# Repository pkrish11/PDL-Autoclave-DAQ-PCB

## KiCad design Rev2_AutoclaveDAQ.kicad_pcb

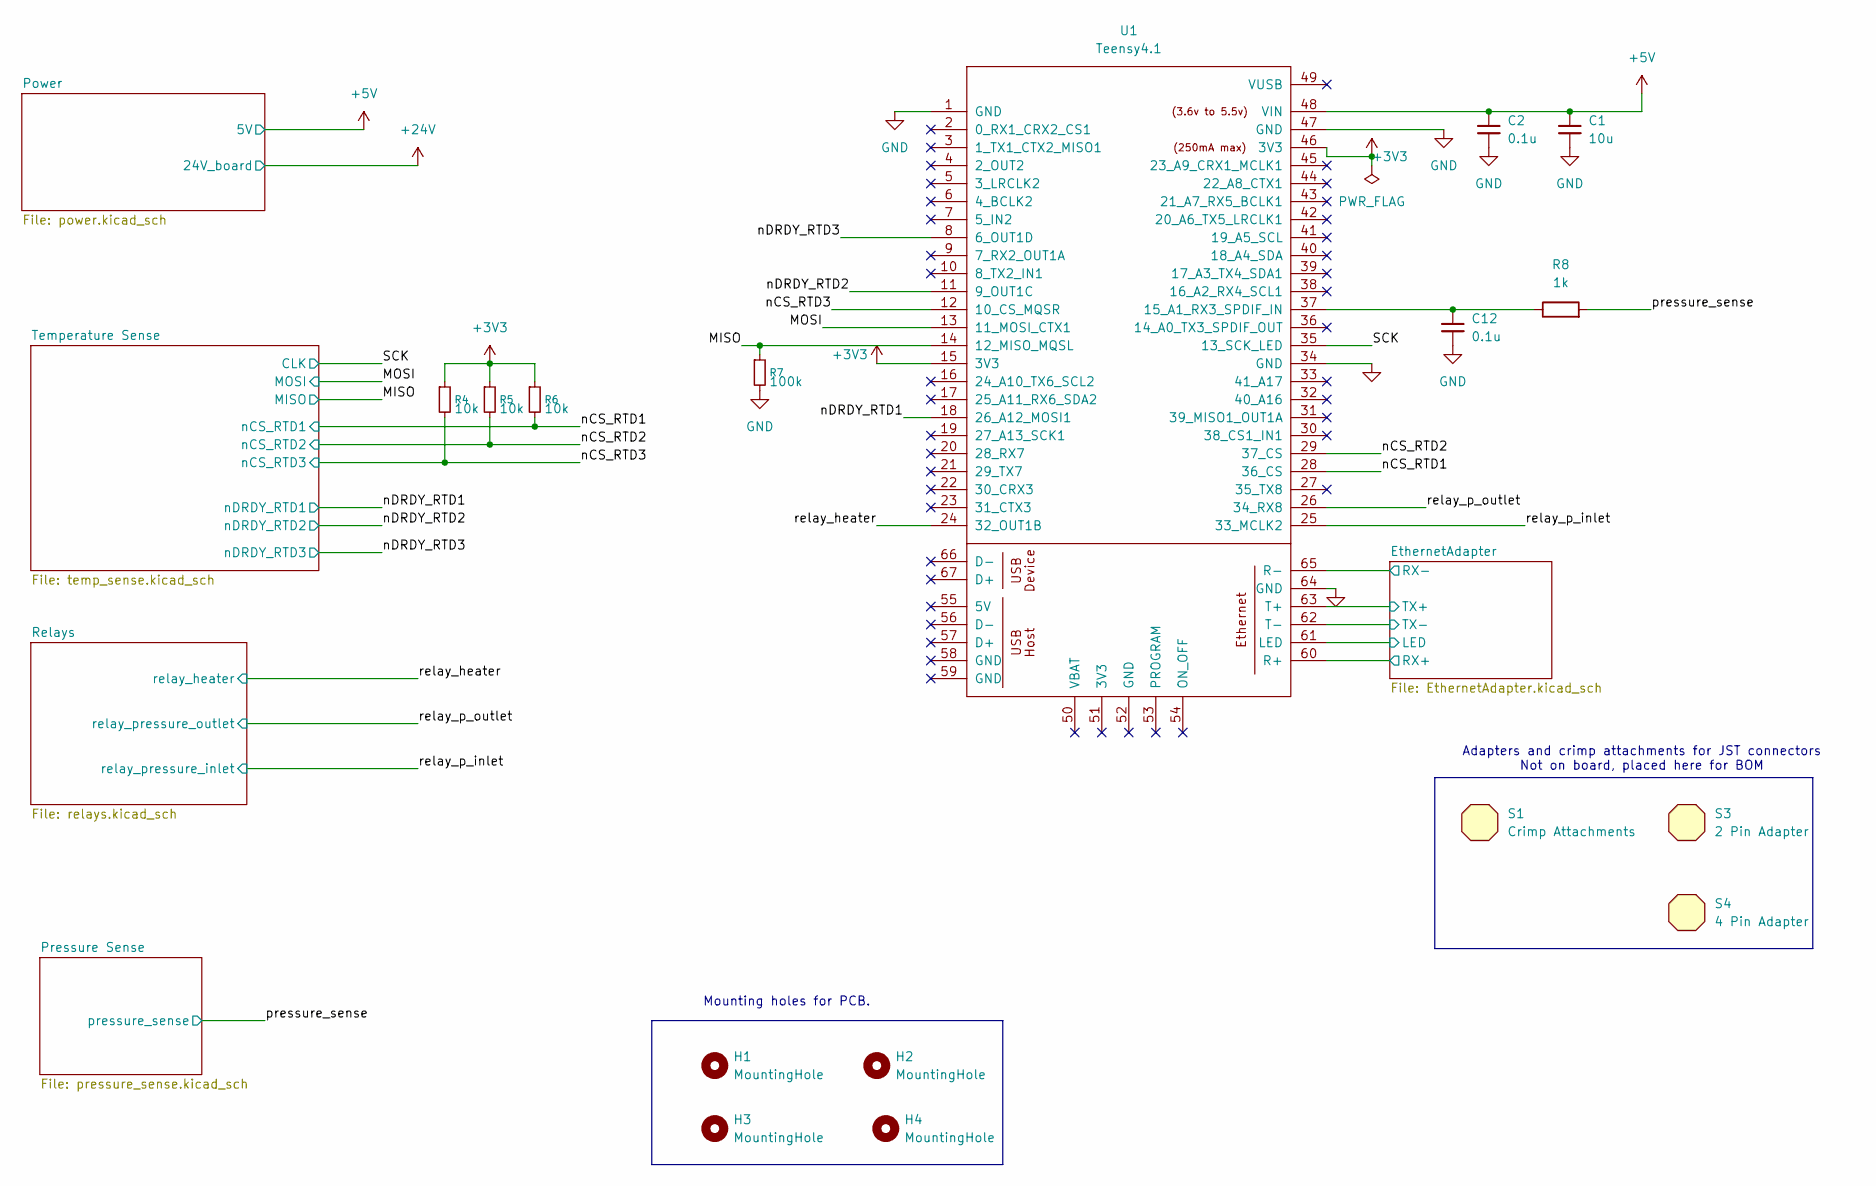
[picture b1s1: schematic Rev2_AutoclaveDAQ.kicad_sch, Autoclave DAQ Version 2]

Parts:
C1: 10u; C_0805_2012Metric; DigiKey_Part_Number 1276-2872-1-ND
C2, C12: 0.1u; C_0805_2012Metric; DigiKey_Part_Number 399-C0805C104K5RACTUCT-ND
H1, H2, H3, H4: MountingHole; MountingHole_3.2mm_M3
R4, R5, R6: 10k; R_0805_2012Metric; DigiKey_Part_Number RMCF0805FT10K0CT-ND
R7: 100k; R_0805_2012Metric; DigiKey_Part_Number P100KDACT-ND
R8: 1k; R_0805_2012Metric; DigiKey_Part_Number 541-1.00KCCT-ND
S1: Crimp Attachments; DigiKey_Part_Number 455-1135TR-ND
S3: 2 Pin Adapter; DigiKey_Part_Number 455-2266-ND
S4: 4 Pin Adapter; DigiKey_Part_Number 455-2267-ND
U1: Teensy4.1; Teensy41

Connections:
+3V3: R4.1, R5.1, R6.1, U1.15 (3V3), U1.46 (3V3); also elsewhere on the board
+5V: C1.1, C2.1, U1.48 (VIN); also elsewhere on the board
/EthernetAdapter/LED: U1.61 (LED); also elsewhere on the board
/EthernetAdapter/RX+: U1.60 (R+); also elsewhere on the board
/EthernetAdapter/RX-: U1.65 (R-); also elsewhere on the board
/EthernetAdapter/TX+: U1.63 (T+); also elsewhere on the board
/EthernetAdapter/TX-: U1.62 (T-); also elsewhere on the board
/MISO: R7.1, U1.14 (12_MISO_MQSL); also elsewhere on the board
/MOSI: U1.13 (11_MOSI_CTX1); also elsewhere on the board
/SCK: U1.35 (13_SCK_LED); also elsewhere on the board
/nCS_RTD1: R6.2, U1.28 (36_CS); also elsewhere on the board
/nCS_RTD2: R5.2, U1.29 (37_CS); also elsewhere on the board
/nCS_RTD3: R4.2, U1.12 (10_CS_MQSR); also elsewhere on the board
/nDRDY_RTD1: U1.18 (26_A12_MOSI1); also elsewhere on the board
/nDRDY_RTD2: U1.11 (9_OUT1C); also elsewhere on the board
/nDRDY_RTD3: U1.8 (6_OUT1D); also elsewhere on the board
/pressure_sense: R8.2; also elsewhere on the board
/relay_heater: U1.24 (32_OUT1B); also elsewhere on the board
/relay_p_inlet: U1.25 (33_MCLK2); also elsewhere on the board
/relay_p_outlet: U1.26 (34_RX8); also elsewhere on the board
GND: C1.2, C2.2, C12.2, R7.2, U1.1 (GND), U1.34 (GND), U1.47 (GND), U1.64 (GND); also elsewhere on the board
unnamed: C12.1, R8.1, U1.37 (15_A1_RX3_SPDIF_IN)

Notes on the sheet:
Adapters and crimp attachments for JST connectors Not on board, placed here for BOM
Mounting holes for PCB.

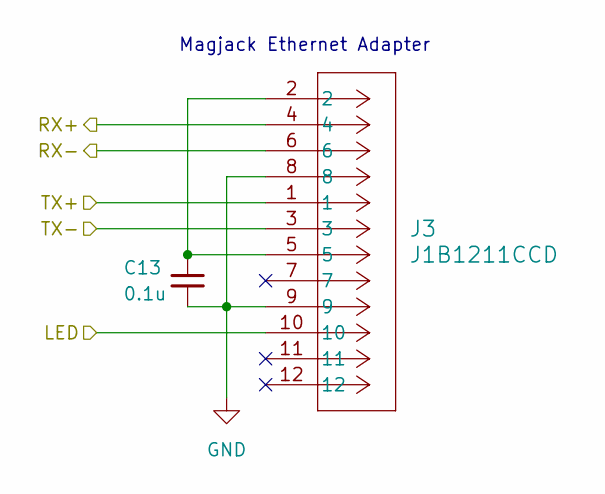
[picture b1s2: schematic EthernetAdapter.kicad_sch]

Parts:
C13: 0.1u; C_0805_2012Metric; DigiKey_Part_Number 399-C0805C104K5RACTUCT-ND
J3: J1B1211CCD; CONN12_J1B1211CCD_WIZ

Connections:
/EthernetAdapter/LED: J3.10; also elsewhere on the board
/EthernetAdapter/RX+: J3.4; also elsewhere on the board
/EthernetAdapter/RX-: J3.6; also elsewhere on the board
/EthernetAdapter/TX+: J3.1; also elsewhere on the board
/EthernetAdapter/TX-: J3.3; also elsewhere on the board
GND: C13.2, J3.8, J3.9; also elsewhere on the board
unnamed: C13.1, J3.2, J3.5

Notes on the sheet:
Magjack Ethernet Adapter

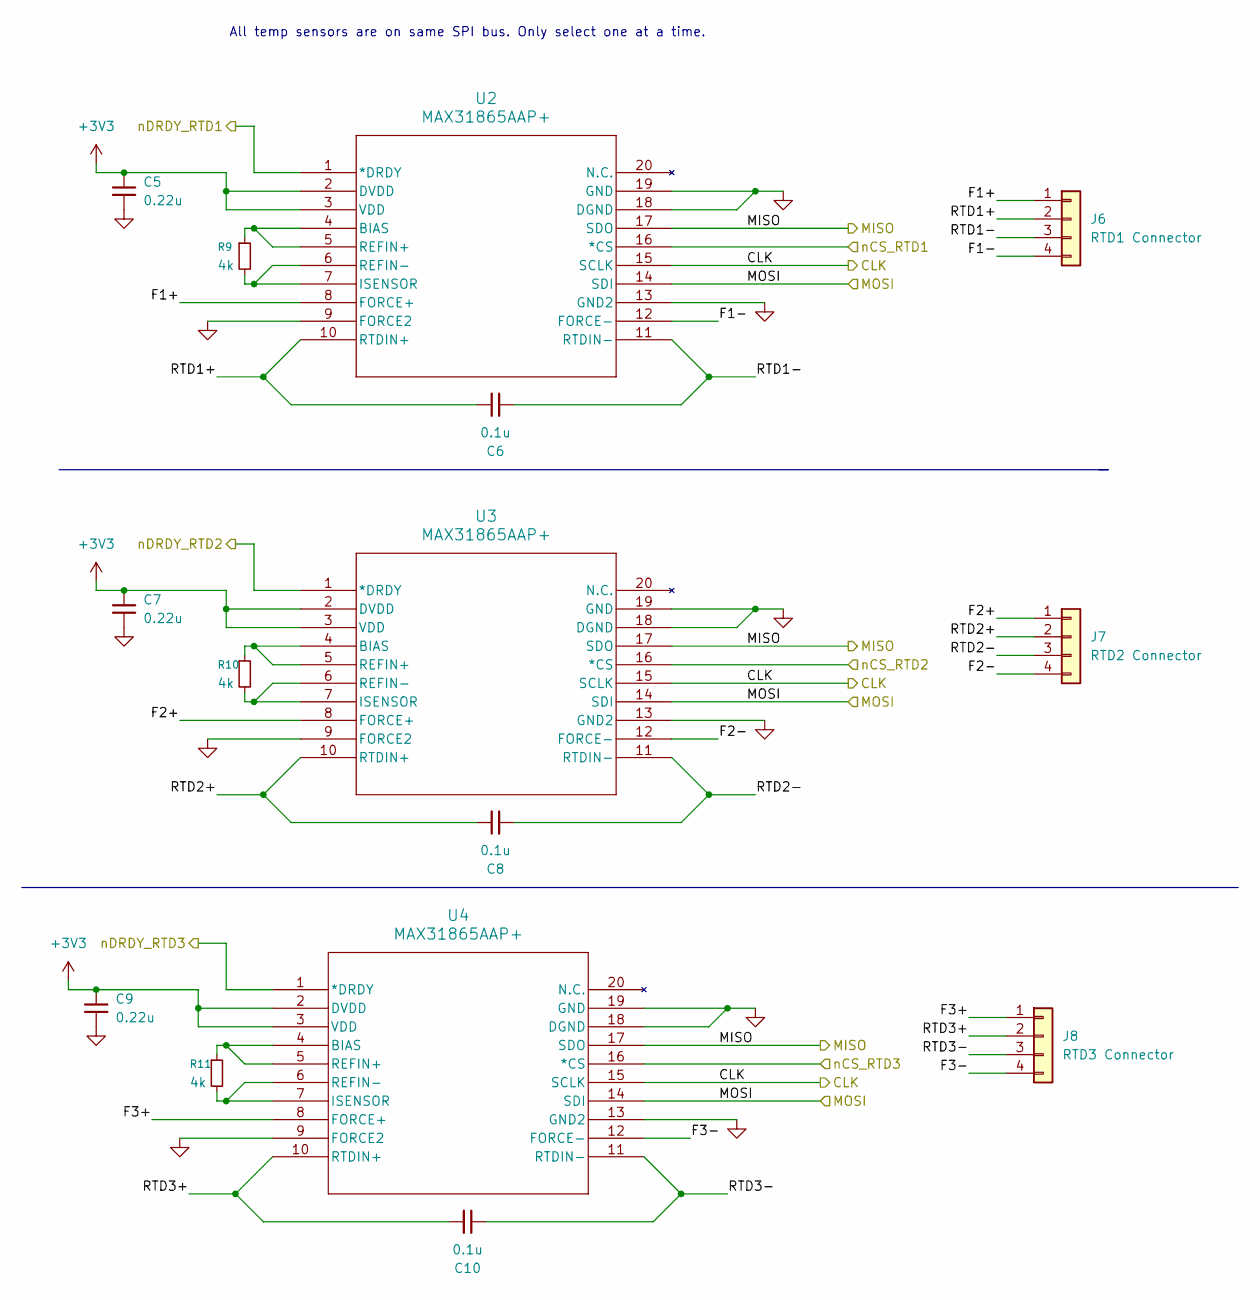
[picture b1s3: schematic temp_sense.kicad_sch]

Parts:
C5, C7, C9: 0.22u; C_0805_2012Metric; DigiKey_Part_Number 399-C0805C224K5RACTUCT-ND
C6, C8, C10: 0.1u; C_0805_2012Metric; DigiKey_Part_Number 399-C0805C104K5RACTUCT-ND
J6: RTD1 Connector; JST_XH_B4B-XH-A_1x04_P2.50mm_Vertical; DigiKey_Part_Number 455-B4B-XH-A-ND
J7: RTD2 Connector; JST_XH_B4B-XH-A_1x04_P2.50mm_Vertical; DigiKey_Part_Number 455-B4B-XH-A-ND
J8: RTD3 Connector; JST_XH_B4B-XH-A_1x04_P2.50mm_Vertical; DigiKey_Part_Number 455-B4B-XH-A-ND
R9, R10, R11: 4k; R_0805_2012Metric; DigiKey_Part_Number 738-RNCF0805BTY4K00CT-ND
U2, U3, U4: MAX31865AAP+; 21-0056C_20_MXM-M; DigiKey_Part_Number MAX31865AAP+

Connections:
+3V3: C5.1, C7.1, C9.1, U2.2 (DVDD), U2.3 (VDD), U3.2 (DVDD), U3.3 (VDD), U4.2 (DVDD), U4.3 (VDD); also elsewhere on the board
/MISO: U2.17 (SDO), U3.17 (SDO), U4.17 (SDO); also elsewhere on the board
/MOSI: U2.14 (SDI), U3.14 (SDI), U4.14 (SDI); also elsewhere on the board
/SCK: U2.15 (SCLK), U3.15 (SCLK), U4.15 (SCLK); also elsewhere on the board
/Temperature Sense/F1+: J6.1, U2.8 (FORCE+)
/Temperature Sense/F1-: J6.4, U2.12 (FORCE-)
/Temperature Sense/F2+: J7.1, U3.8 (FORCE+)
/Temperature Sense/F2-: J7.4, U3.12 (FORCE-)
/Temperature Sense/F3+: J8.1, U4.8 (FORCE+)
/Temperature Sense/F3-: J8.4, U4.12 (FORCE-)
/Temperature Sense/RTD1+: C6.1, J6.2, U2.10 (RTDIN+)
/Temperature Sense/RTD1-: C6.2, J6.3, U2.11 (RTDIN-)
/Temperature Sense/RTD2+: C8.1, J7.2, U3.10 (RTDIN+)
/Temperature Sense/RTD2-: C8.2, J7.3, U3.11 (RTDIN-)
/Temperature Sense/RTD3+: C10.1, J8.2, U4.10 (RTDIN+)
/Temperature Sense/RTD3-: C10.2, J8.3, U4.11 (RTDIN-)
/nCS_RTD1: U2.16 (*CS); also elsewhere on the board
/nCS_RTD2: U3.16 (*CS); also elsewhere on the board
/nCS_RTD3: U4.16 (*CS); also elsewhere on the board
/nDRDY_RTD1: U2.1 (*DRDY); also elsewhere on the board
/nDRDY_RTD2: U3.1 (*DRDY); also elsewhere on the board
/nDRDY_RTD3: U4.1 (*DRDY); also elsewhere on the board
GND: C5.2, C7.2, C9.2, U2.9 (FORCE2), U2.13 (GND2), U2.18 (DGND), U2.19 (GND), U3.9 (FORCE2), U3.13 (GND2), U3.18 (DGND), U3.19 (GND), U4.9 (FORCE2), U4.13 (GND2), U4.18 (DGND), U4.19 (GND); also elsewhere on the board
unnamed: R9.1, U2.4 (BIAS), U2.5 (REFIN+)
unnamed: R9.2, U2.6 (REFIN-), U2.7 (ISENSOR)
unnamed: R10.1, U3.4 (BIAS), U3.5 (REFIN+)
unnamed: R10.2, U3.6 (REFIN-), U3.7 (ISENSOR)
unnamed: R11.1, U4.4 (BIAS), U4.5 (REFIN+)
unnamed: R11.2, U4.6 (REFIN-), U4.7 (ISENSOR)

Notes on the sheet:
All temp sensors are on same SPI bus. Only select one at a time.

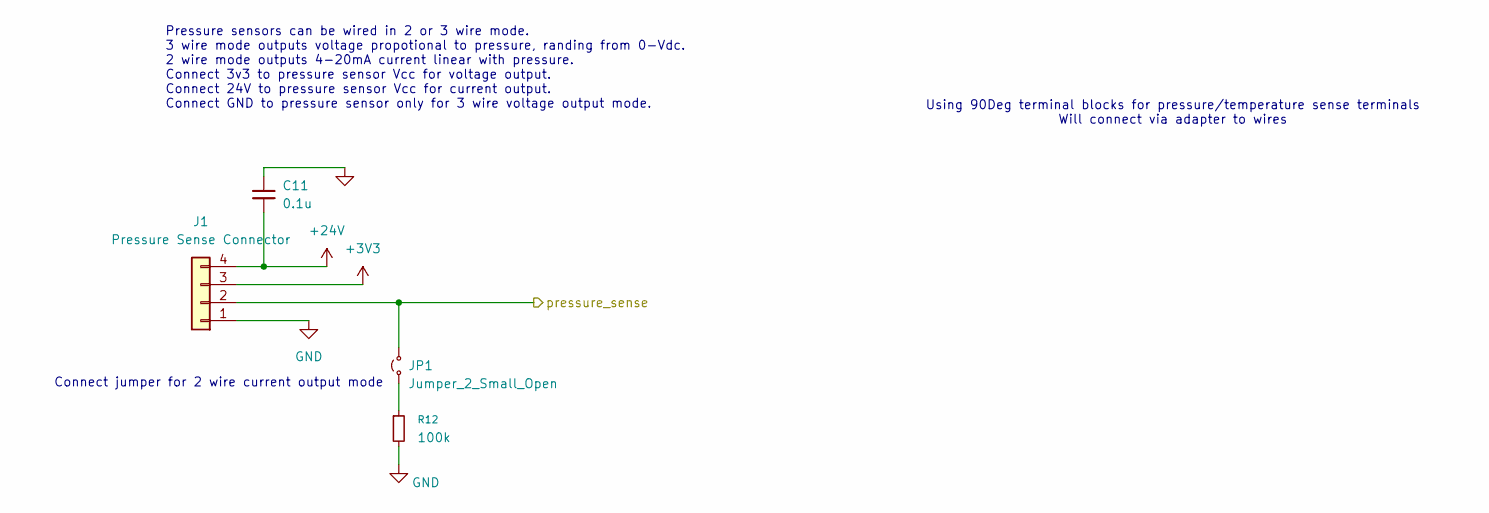
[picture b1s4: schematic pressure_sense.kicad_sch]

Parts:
C11: 0.1u; C_0805_2012Metric; DigiKey_Part_Number 399-C0805C104K5RACTUCT-ND
J1: Pressure Sense Connector; JST_XH_B4B-XH-A_1x04_P2.50mm_Vertical; DigiKey_Part_Number 455-B4B-XH-A-ND
JP1: Jumper_2_Small_Open; PinHeader_1x02_P2.54mm_Vertical
R12: 100k; R_0805_2012Metric; DigiKey_Part_Number P100KDACT-ND

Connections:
+3V3: J1.3; also elsewhere on the board
+24V: C11.2, J1.4; also elsewhere on the board
/pressure_sense: J1.2, JP1.2 (B); also elsewhere on the board
GND: C11.1, J1.1, R12.2; also elsewhere on the board
unnamed: JP1.1 (A), R12.1

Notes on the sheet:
Connect jumper for 2 wire current output mode
Using 90Deg terminal blocks for pressure/temperature sense terminals Will connect via adapter to wires
Pressure sensors can be wired in 2 or 3 wire mode. 3 wire mode outputs voltage propotional to pressure, randing from 0-Vdc. 2 wire mode outputs 4-20mA current linear with pressure. Connect 3v3 to pressure sensor Vcc for voltage output. Connect 24V to pressure sensor Vcc for current output. Connect 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

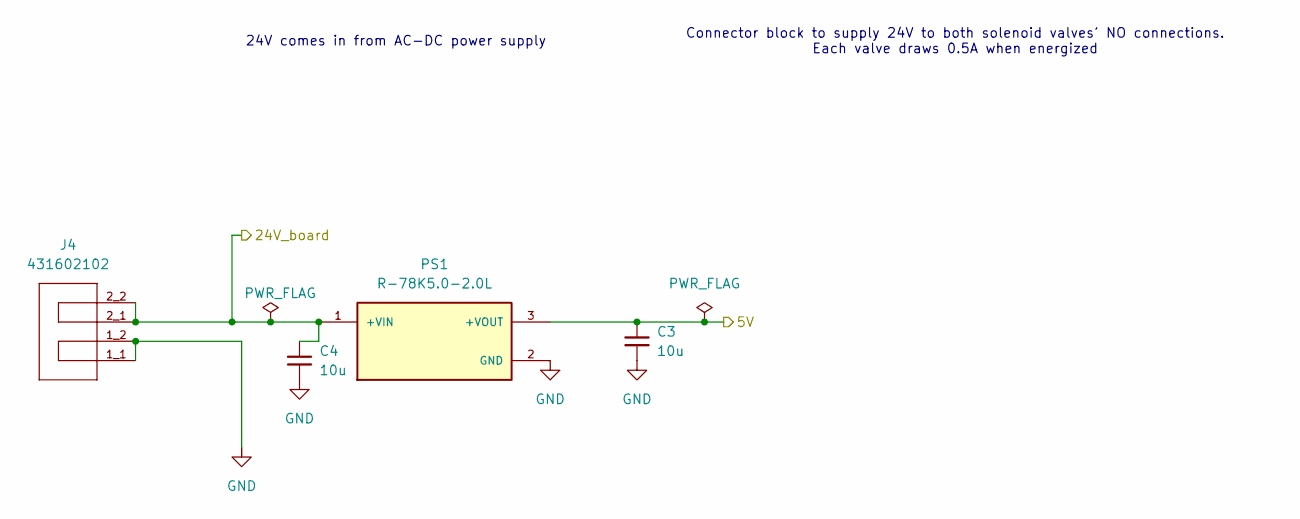
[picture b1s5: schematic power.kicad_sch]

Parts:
C3, C4: 10u; C_0805_2012Metric; DigiKey_Part_Number 1276-2872-1-ND
J4: 431602102; molex_connector; MPN 431602102; DigiKey_Part_Number WM18478-ND
PS1: R-78K5.0-2.0L; CONV_R-78K5.0-2.0L; PARTREV 1; DigiKey_Part_Number 945-R-78K5.0-2.0L-ND

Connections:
+5V: C3.1, PS1.3 (+VOUT); also elsewhere on the board
+24V: C4.1, J4.2_1, J4.2_2, PS1.1 (+VIN); also elsewhere on the board
GND: C3.2, C4.2, J4.1_1, J4.1_2, PS1.2 (GND); also elsewhere on the board

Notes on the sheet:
24V comes in from AC-DC power supply
Connector block to supply 24V to both solenoid valves' NO connections. Each valve draws 0.5A when energized

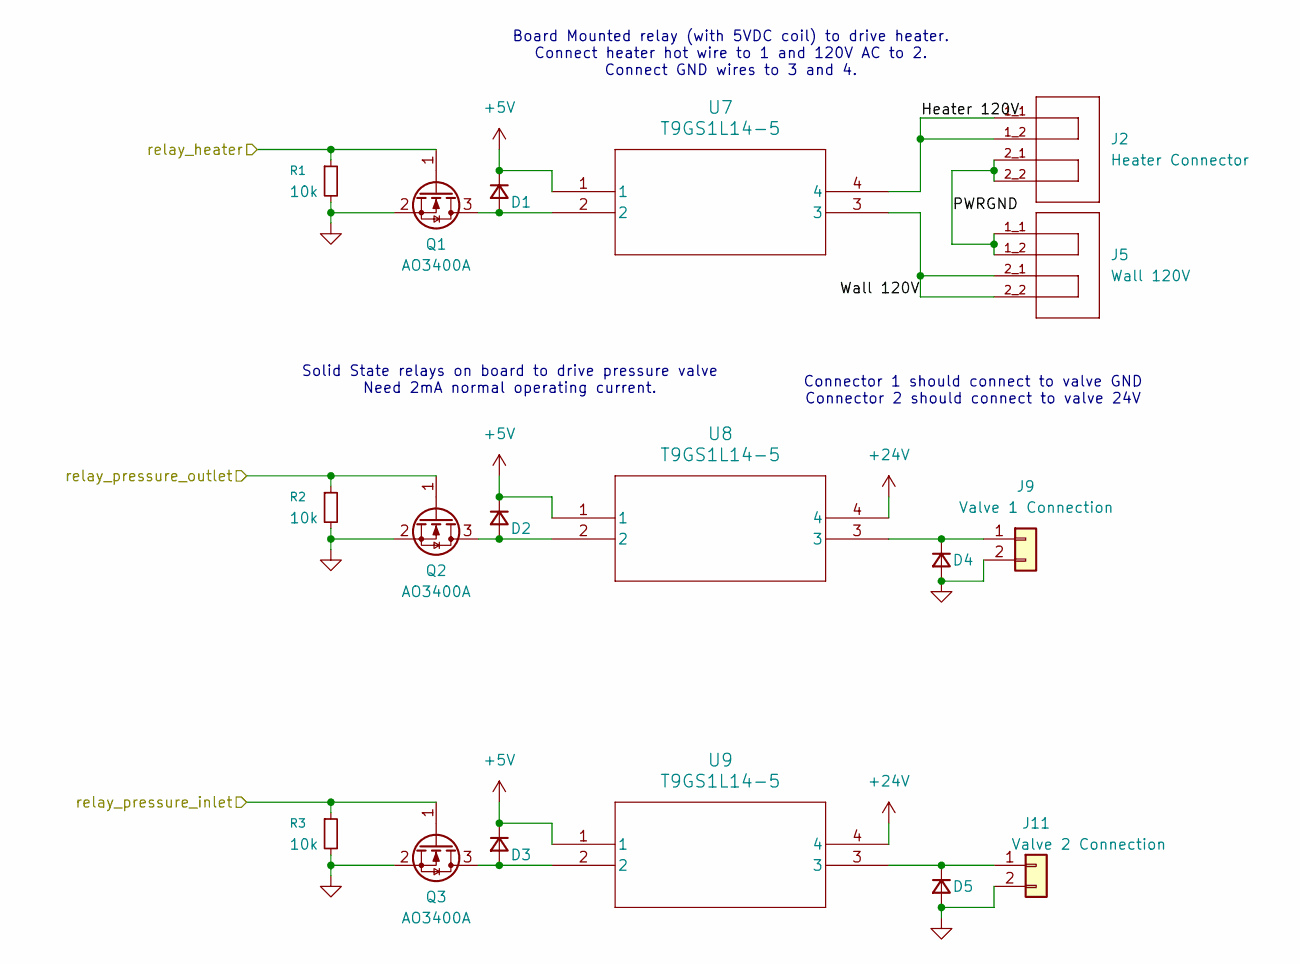
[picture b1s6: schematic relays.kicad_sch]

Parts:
D1, D2, D3, D4, D5: Freewheeling diode; SMA_403AE_OSI-L; DigiKey_Part_Number S1BFSCT-ND
J2: Heater Connector; molex_connector; MPN 431602102
J5: Wall 120V; molex_connector; MPN 431602102
J9: Valve 1 Connection; JST_XH_B2B-XH-A_1x02_P2.50mm_Vertical
J11: Valve 2 Connection; JST_XH_B2B-XH-A_1x02_P2.50mm_Vertical
Q1, Q2, Q3: AO3400A; SOT-23; DigiKey_Part_Number 785-1000-1-ND
R1, R2, R3: 10k; R_0805_2012Metric
U7, U8, U9: T9GS1L14-5; RELAY5_T9GS1L14-5_TEC; DigiKey_Part_Number PB2389-ND

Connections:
+5V: D1.1 (K), D2.1 (K), D3.1 (K), U7.1, U8.1, U9.1; also elsewhere on the board
+24V: U8.4, U9.4; also elsewhere on the board
/Relays/Heater 120V: J2.1_1, J2.1_2, U7.4
/Relays/PWRGND: J2.2_1, J2.2_2, J5.1_1, J5.1_2
/Relays/Wall 120V: J5.2_1, J5.2_2, U7.3
/relay_heater: Q1.1 (G), R1.1; also elsewhere on the board
/relay_p_inlet: Q3.1 (G), R3.1; also elsewhere on the board
/relay_p_outlet: Q2.1 (G), R2.1; also elsewhere on the board
GND: D4.2 (A), D5.2 (A), J9.2, J11.2, Q1.2 (S), Q2.2 (S), Q3.2 (S), R1.2, R2.2, R3.2; also elsewhere on the board
unnamed: D1.2 (A), Q1.3 (D), U7.2
unnamed: D2.2 (A), Q2.3 (D), U8.2
unnamed: D3.2 (A), Q3.3 (D), U9.2
unnamed: D4.1 (K), J9.1, U8.3
unnamed: D5.1 (K), J11.1, U9.3

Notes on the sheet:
Board Mounted relay (with 5VDC coil) to drive heater. Connect heater hot wire to 1 and 120V AC to 2. Connect GND wires to 3 and 4.
Solid State relays on board to drive pressure valve Need 2mA normal operating current.
Connector 1 should connect to valve GND Connector 2 should connect to valve 24V

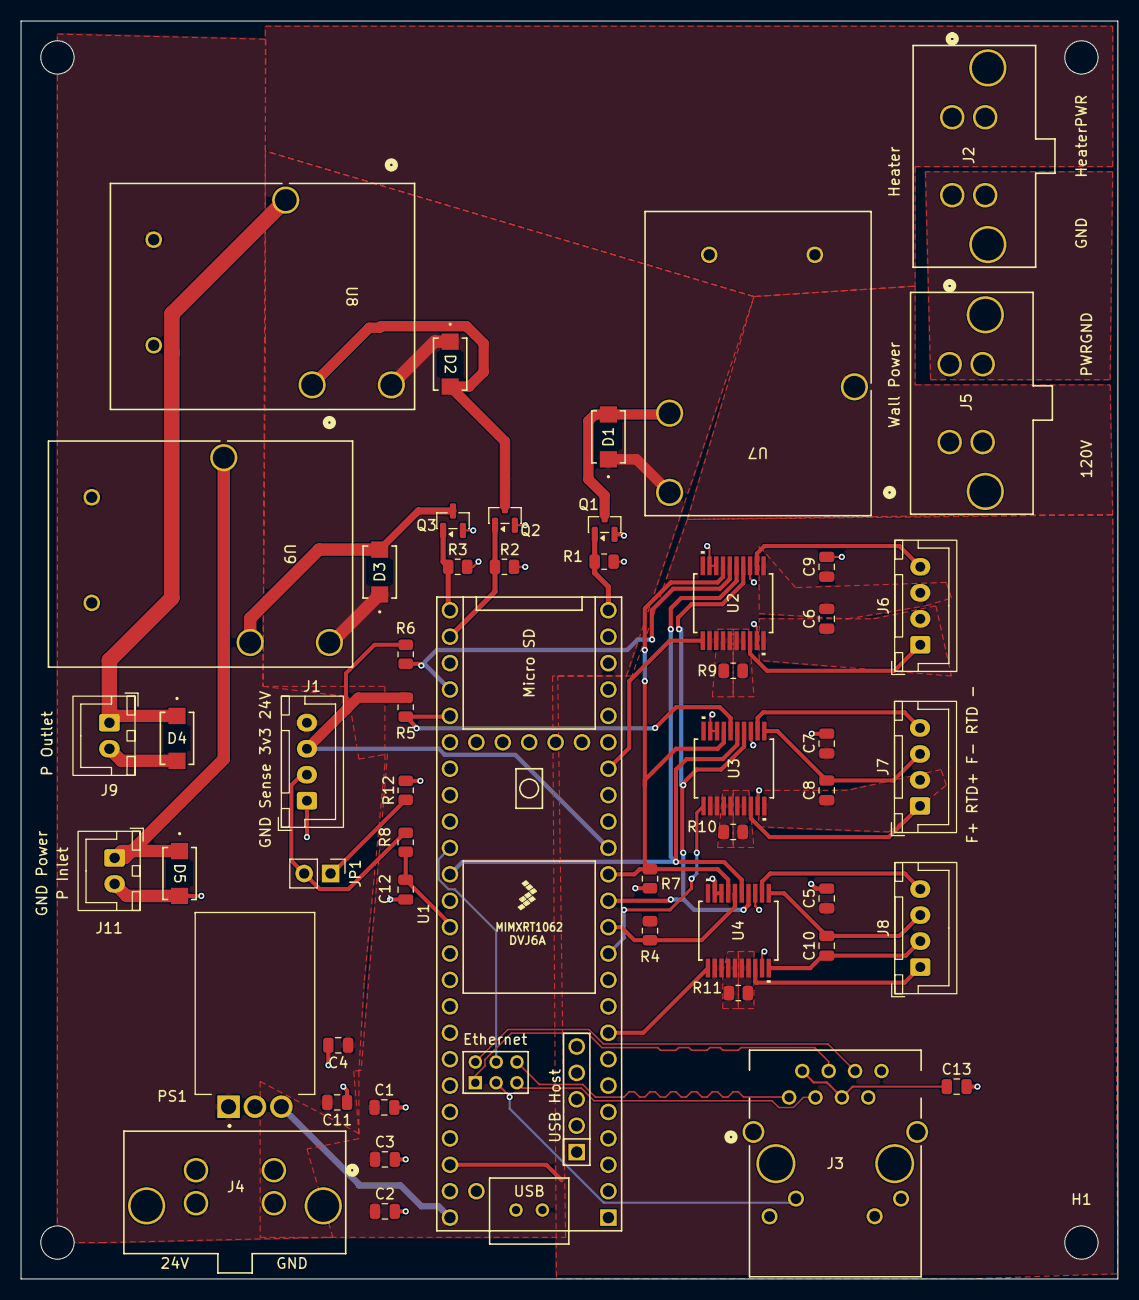
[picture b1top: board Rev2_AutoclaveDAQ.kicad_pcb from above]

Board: 2 copper layers, 105.5 x 121.0 mm, 56 parts (0 on the bottom side), 51 nets.

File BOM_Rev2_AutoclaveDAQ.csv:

Reference,Qty,Value,DNP,Exclude from BOM,Exclude from Board,Exclude from Simulation,Exclude from Position Files,Footprint,Datasheet,DigiKey_Part_Number,,,Actual Quantity,,Notes
"C1,C3,C4",3,10u,,,,,${EXCLUDE_FROM_POS_FILES},Capacitor_SMD:C_0805_2012Metric,https://mm.digikey.com/Volume0/opasdata/d220001/medias/docus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,1276-2872-1-ND,,,8,,Parts counted as per 2 boards
"C2,C6,C8,C10,C11,C12,C13",7,0.1u,,,,,${EXCLUDE_FROM_POS_FILES},Capacitor_SMD:C_0805_2012Metric,https://yageogroup.com/content/datasheet/asset/file/KEM_C100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,399-C0805C104K5RACTUCT-ND,,,16,,
"C5,C7,C9",3,0.22u,,,,,${EXCLUDE_FROM_POS_FILES},Capacitor_SMD:C_0805_2012Metric,https://yageogroup.com/content/datasheet/asset/file/KEM_C100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,399-C0805C224K5RACTUCT-ND,,,8,,
"D1,D2,D3,D4,D5",5,Freewheeling diode,,,,,${EXCLUDE_FROM_POS_FILES},PDL_kicad_footprints:SMA_403AE_OSI-L,https://www.onsemi.com/pub/Collateral/S1M-D.PDF,S1BFSCT-ND,,,12,,
"J1,J6,J7,J8",4,"Pressure Sense Connector,RTD1 Connector,RTD2 Connector,RTD3 Connector",,,,,${EXCLUDE_FROM_POS_FILES},Connector_JST:JST_XH_B4B-XH-A_1x04_P2.50mm_Vertical,https://www.jst-mfg.com/product/pdf/eng/eXH.pdf,455-B4B-XH-A-ND,,,10,,
"J2,J5",2,"Heater Connector,Wall 120V",,,,,${EXCLUDE_FROM_POS_FILES},PDL_kicad_footprints:molex_connector,https://s3.amazonaws.com/snapeda/datasheet/431602102_Molex.pdf,,,,6,,
J3,1,J1B1211CCD,,,,,${EXCLUDE_FROM_POS_FILES},PDL_kicad_footprints:CONN12_J1B1211CCD_WIZ,https://cdn.sparkfun.com/assets/0/4/9/9/a/DS-18615-Ethernet_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,,,,4,,
J4,1,431602102,,,,,${EXCLUDE_FROM_POS_FILES},PDL_kicad_footprints:molex_connector,https://s3.amazonaws.com/snapeda/datasheet/431602102_Molex.pdf,WM18478-ND,,,4,,
"J9,J11",2,"Valve 1 Connection,Valve 2 Connection",,,,,${EXCLUDE_FROM_POS_FILES},Connector_JST:JST_XH_B2B-XH-A_1x02_P2.50mm_Vertical,https://www.jst-mfg.com/product/pdf/eng/eXH.pdf,,,,6,,
PS1,1,R-78K5.0-2.0L,,,,,${EXCLUDE_FROM_POS_FILES},PDL_kicad_footprints:CONV_R-78K5.0-2.0L,,945-R-78K5.0-2.0L-ND,,,2,,2 Power supply modules
"Q1,Q2,Q3",3,AO3400A,,,,,${EXCLUDE_FROM_POS_FILES},Package_TO_SOT_SMD:SOT-23,http://www.aosmd.com/pdfs/datasheet/AO3400A.pdf,785-1000-1-ND,,,8,,
"R1,R2,R3",3,10k,,,,,${EXCLUDE_FROM_POS_FILES},Resistor_SMD:R_0805_2012Metric,,,,,8,,
"R4,R5,R6",3,10k,,,,,${EXCLUDE_FROM_POS_FILES},Resistor_SMD:R_0805_2012Metric,https://www.seielect.com/catalog/SEI-RMCF_RMCP.pdf,RMCF0805FT10K0CT-ND,,,8,,
"R7,R12",2,100k,,,,,${EXCLUDE_FROM_POS_FILES},Resistor_SMD:R_0805_2012Metric,https://industrial.panasonic.com/cdbs/www-data/pdf/RDM0000/A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,P100KDACT-ND,,,6,,
R8,1,1k,,,,,${EXCLUDE_FROM_POS_FILES},Resistor_SMD:R_0805_2012Metric,https://www.vishay.com/docs/20035/dcrcwe3.pdf,541-1.00KCCT-ND,,,4,,
"R9,R10,R11",3,4k,,,,,${EXCLUDE_FROM_POS_FILES},Resistor_SMD:R_0805_2012Metric,https://www.seielect.com/catalog/SEI-RNCF.pdf,738-RNCF0805BTY4K00CT-ND,,,8,,
S1,1,Crimp Attachments,,,Excluded from board,Excluded from simulation,${EXCLUDE_FROM_POS_FILES},,https://www.jst-mfg.com/product/pdf/eng/eXH.pdf,455-1135TR-ND,,,50,,
S3,1,2 Pin Adapter,,,Excluded from board,Excluded from simulation,${EXCLUDE_FROM_POS_FILES},,,455-2266-ND,,,6,,
S4,1,4 Pin Adapter,,,Excluded from board,Excluded from simulation,${EXCLUDE_FROM_POS_FILES},,,455-2267-ND,,,10,,
"U2,U3,U4",3,MAX31865AAP+,,,,,${EXCLUDE_FROM_POS_FILES},PDL_kicad_footprints:21-0056C_20_MXM-M,MAX31865AAP+,MAX31865AAP+,,,7,,
"U7,U8,U9",3,T9GS1L14-5,,,,,${EXCLUDE_FROM_POS_FILES},PDL_kicad_footprints:RELAY5_T9GS1L14-5_TEC,https://www.te.com/commerce/DocumentDelivery/DDEController?A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,PB2389-ND,,,5,,5 Relays
,3,Molex 2 pinAdapter,,,,,,,,WM18463-ND,,,6,,
,6,Molex Crimp Attachments,,,,,,,,WM9174CT-ND,,,12,,
